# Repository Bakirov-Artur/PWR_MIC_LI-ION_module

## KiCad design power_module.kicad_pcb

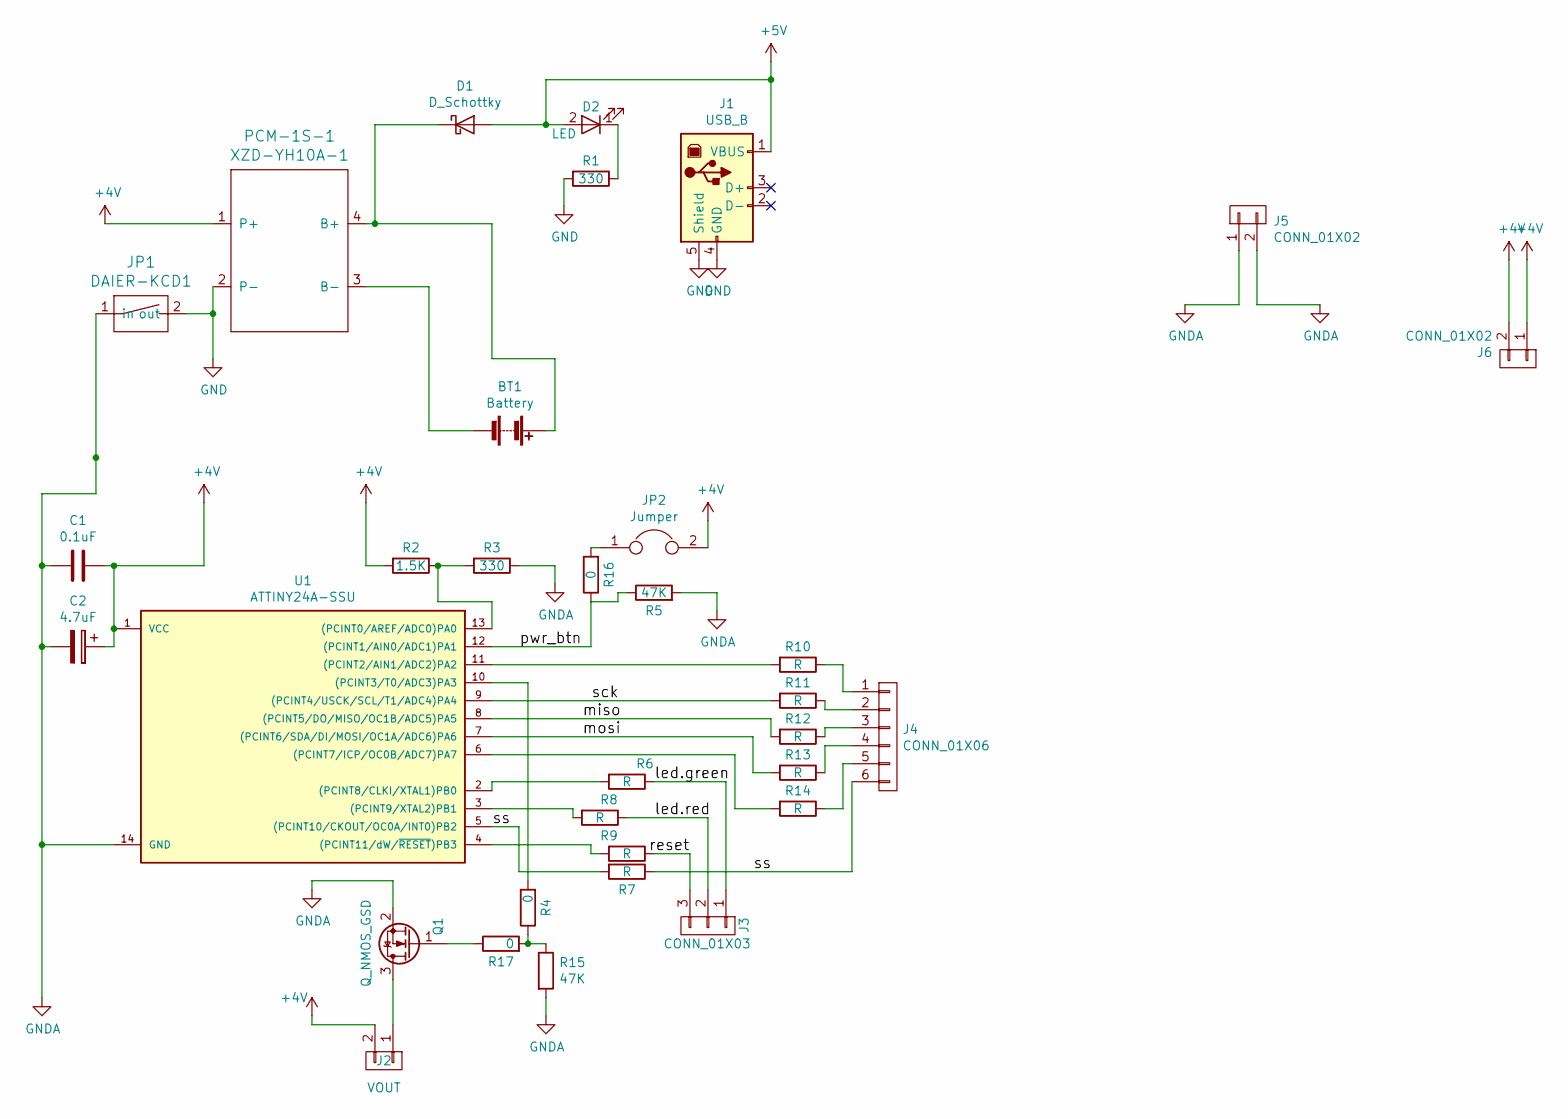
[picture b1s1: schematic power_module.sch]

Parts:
BT1: Battery; BH-18650-PC4
C1: 0.1uF; C_0805
C2: 4.7uF; CP_Tantalum_Case-D_EIA-7343-31_Reflow
D1: D_Schottky; D_DO-201AD_P15.24mm_Horizontal
D2: LED; LED_D3.0mm_Horizontal_O3.81mm_Z6.0mm
J1: USB_B
J2: VOUT; Pin_Header_Angled_1x02_Pitch2.54mm
J3: CONN_01X03; Pin_Header_Straight_1x03_Pitch2.54mm
J4: CONN_01X06; Pin_Header_Straight_1x06_Pitch2.54mm
J5, J6: CONN_01X02; R_2512
JP1: DAIER-KCD1; Daier_KCD1
JP2: Jumper; Pin_Header_Straight_1x02_Pitch2.54mm
PCM-1S-1: XZD-YH10A-1
Q1: Q_NMOS_GSD; SOT-23
R1, R3: 330; R_1206
R2: 1.5K; R_1206
R4, R16: 0; R_1206
R5, R15: 47K; R_1206
R6, R7, R8, R9, R10, R11, R12, R13, R14: R; R_1206
R17: 0; R_2512
U1: ATTINY24A-SSU; SOIC-14_3.9x8.7mm_Pitch1.27mm

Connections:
+4V: C1.1, C2.1, J2.2, J6.1, J6.2, JP2.2, PCM-1S-1.1 (P+), R2.2, U1.1 (VCC)
+5V: D1.2 (A), D2.2 (A), J1.1 (VBUS)
/led.green: J3.1, R6.1
/led.red: J3.2, R8.1
/miso: R12.2, U1.8 ((PCINT5/DO/MISO/OC1B/ADC5)PA5)
/mosi: R13.2, U1.7 ((PCINT6/SDA/DI/MOSI/OC1A/ADC6)PA6)
/pwr_btn: R5.1, R16.1, U1.12 ((PCINT1/AIN0/ADC1)PA1)
/reset: J3.3, R9.1
/sck: R11.2, U1.9 ((PCINT4/USCK/SCL/T1/ADC4)PA4)
GND: J1.4 (GND), J1.5 (Shield), JP1.2 (out), PCM-1S-1.2 (P-), R1.2
GNDA: C1.2, C2.2, J5.1, J5.2, JP1.1 (in), Q1.2 (S), R3.1, R5.2, R15.2, U1.14 (GND)
unnamed: BT1.1 (+), D1.1 (K), PCM-1S-1.4 (B+)
unnamed: BT1.2 (-), PCM-1S-1.3 (B-)
unnamed: D2.1 (K), R1.1
unnamed: J2.1, Q1.3 (D)
unnamed: J4.1, R10.1
unnamed: J4.2, R11.1
unnamed: J4.3, R12.1
unnamed: J4.4, R13.1
unnamed: J4.5, R14.1
unnamed: JP2.1, R16.2
unnamed: Q1.1 (G), R17.1
unnamed: R2.1, R3.2, U1.13 ((PCINT0/AREF/ADC0)PA0)
unnamed: R4.2, U1.10 ((PCINT3/T0/ADC3)PA3)
unnamed: R6.2, U1.2 ((PCINT8/CLKI/XTAL1)PB0)
unnamed: R8.2, U1.3 ((PCINT9/XTAL2)PB1)
unnamed: R9.2, U1.4 ((PCINT11/dW/~RESET~)PB3)
unnamed: R10.2, U1.11 ((PCINT2/AIN1/ADC2)PA2)
unnamed: R14.2, U1.6 ((PCINT7/ICP/OC0B/ADC7)PA7)
unnamed: R4.1, R15.1, R17.2

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
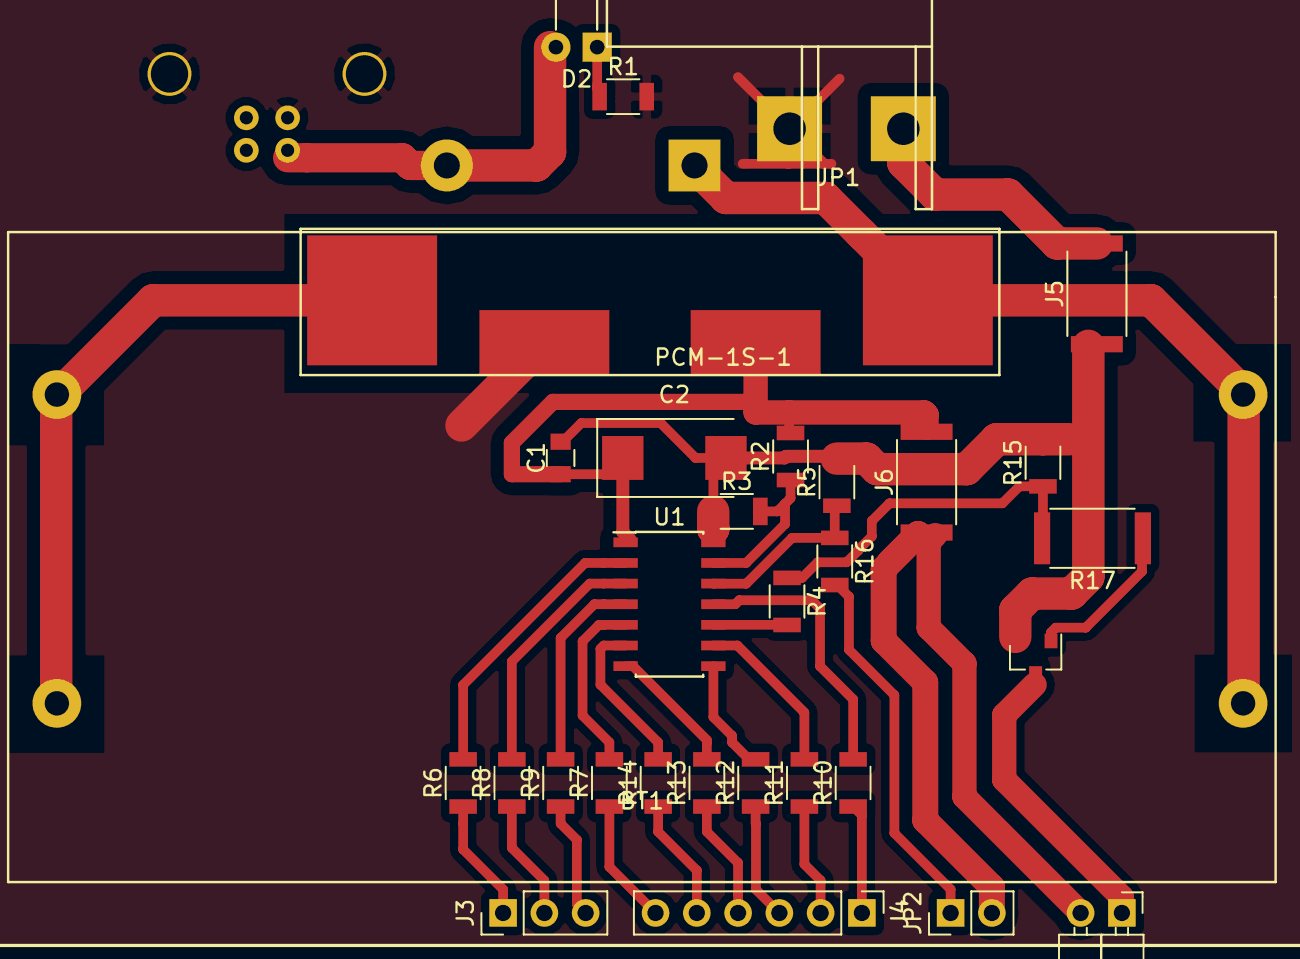
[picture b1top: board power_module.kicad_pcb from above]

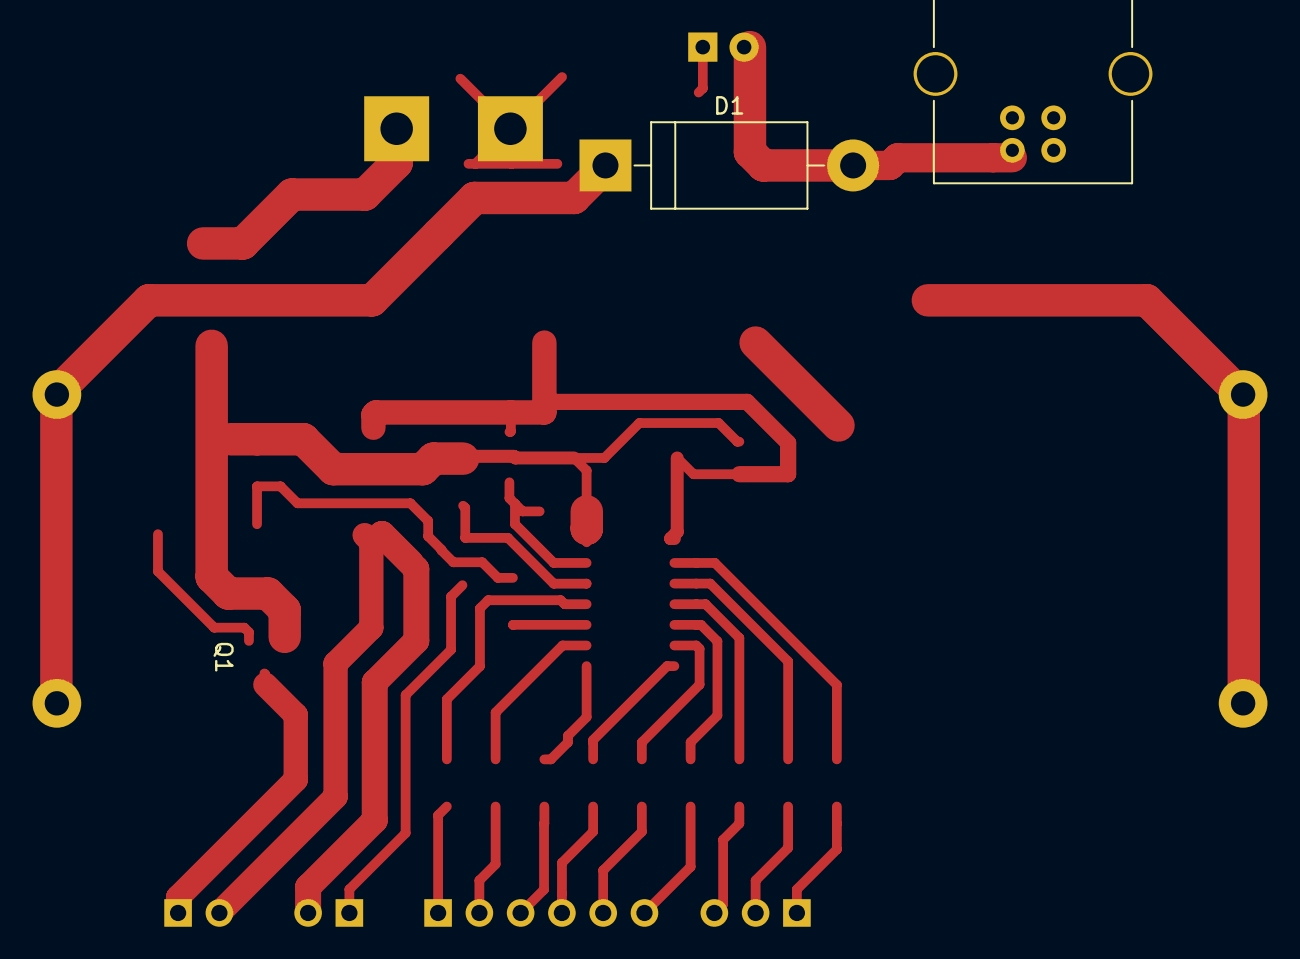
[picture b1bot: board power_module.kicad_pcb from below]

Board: 2 copper layers, 33 parts (2 on the bottom side), 32 nets.

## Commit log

2017-08-01 initial
2017-08-01 merged
2017-08-03 add attiny 24-ssu
2017-08-03 Correct pcb
2017-08-04 make last changes
2017-08-04 Make it one side
2017-08-06 Поправил схему н-канального транзистора, обновил дорожки на плате, удалил не нужные файлы, поправил посадочные места для выключателя, поправил посадочное место для батареии 18650
2017-08-11 Мелкие поправки по плате
2017-08-15 last modify
